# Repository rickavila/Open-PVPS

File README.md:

# Open-PVPS
Open Source Pandemic Virus Protection Systems

Our goal is to develop open source pandemic virus protection technology that will significantly improve the safety of healthcare workers on the front lines of COVID-19.

To achieve this we are working to substantially reduce the manufacturing and operating cost of a PAPR (https://en.wikipedia.org/wiki/Powered_air-purifying_respirator) while maintaining HEPA filter efficiency (99.97% for 3um particles) with a design that can be easily mass produced anywhere in the world using standard commercial manufacturing machinery and automation. All work performed on this project is open source and freely available with a permissive open source license (CC BY-SA 4.0).

This repository contains a directory for "technical reports", a directory for CAD designs, and a directory for the electronics components. 

The technical reports directory contains documents that describe the technical work, calculations, and decisions that have been made for each major PAPR technical area. The major technical areas are:
* Overall PAPR System Specifications and Performance
* Face Shield, Visor, and Drape (coming soon)
* Power and Control Box
* Blower, Gauge, and Diffuser
* Filter

The CAD directory contains CAD files used to deveop the first PVPS prototypes. The file format is Autodesk Fusion 360. In the future we will also post STL files for anyone that would like to print out the 3D printed components.

The electronics directory contains files that define the physical circuit boards for the battery box and the program for the control board microprocessor. All of the electronics were designed by Jim Hannas with inputs from the team.

This project has a website at http://open-pvps.org

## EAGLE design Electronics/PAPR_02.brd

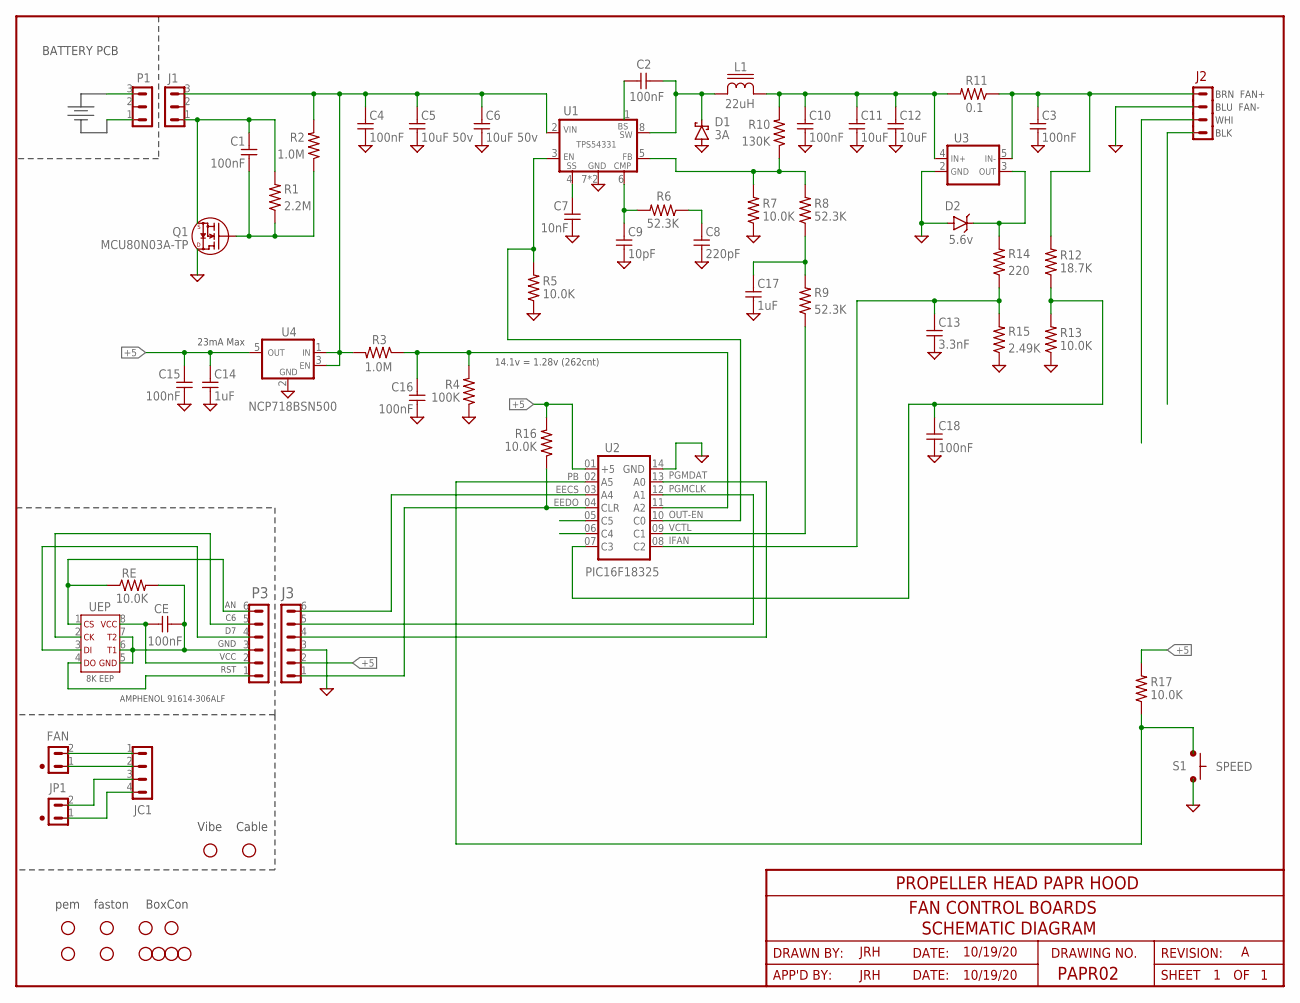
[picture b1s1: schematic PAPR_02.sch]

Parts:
BOM1, BOM2: pem; BOM_ADDER; PART_NUMBER KF2-440-ET
BOM3, BOM4: faston; BOM_ADDER; PART_NUMBER 4901
BOM5: vibrator; BOM_ADDER; PART_NUMBER Z6SCAB0061141
BOM6: BoxCon; BOM_ADDER; PART_NUMBER T4070014041-001
BOM7: Cable; BOM_ADDER; PART_NUMBER 1-2273003-1
BOM8: Plug; BOM_ADDER; PART_NUMBER 1445022-4
BOM9, BOM10, BOM11, BOM12: Pin; BOM_ADDER; PART_NUMBER 1-794606-1
C1, C2, C3, C4, C10, C15, C16, C18: 100nF; R0805; PART_NUMBER CL21B104KBC5PNL 08055C104KAT4A
C5, C6: 10uF 50v; R1210; PART_NUMBER C3225X7R1H106M250AC
C7: 10nF; R0805; PART_NUMBER CL21B103KBANNNC C0805C103K1RAC7210
C8: 220pF; R0805; PART_NUMBER CL21C221JBANNNC C0805C0G500-221JNE
C9: 10pF; R0805; PART_NUMBER C0805C100K5GACTU CML0805C0G100JT50V
C11, C12: 10uF; R1210; PART_NUMBER CL32A106KAULNNE TMK325BJ106KN-T
C13: 3.3nF; R0805; PART_NUMBER C0805C332K5RACTU
C14, C17: 1uF; R0805; PART_NUMBER CL21B105KOFNNNG EMK212B7105KG-T
CE: 100nF; R0805; PART_NUMBER CL21B104KBC5PNL 08055C104KAT4A
D1: 3A; SMA; PART_NUMBER B340A-13-F MBRA340T3G SSA34HE3_A/I
D2: 5.6v; SOT23-3; PART_NUMBER SZBZX84-C5V6LT1G
FAN: Fan_Hdr; 641215-2
J1: bat; 1746142
J2-BLK, J2-BLU, J2-BRN, J2-WHI: WIRE-HDRS200; PADS200
J3: 6p; J06P; PART_NUMBER MTSW-106-22-G-S-350
JC1: Cable_Termination; B4P-VH
JP1: Spare; 641215-2
L1: 22uH; SRU1048
P1: bat; 1746142M
P3: 6p plug; J06P
Q1: MCU80N03A-TP; TO252; PART_NUMBER MCU80N03A-TP DMG4800LK3-13 NTD4969NT4G
R1: 2.2M; R0805; PART_NUMBER RMCF0805FT2M21 CRCW08052M20FKEA
R2: 1.0M; R0805; PART_NUMBER RMCF0805FG1M00 RK73H2ATTD1004F
R3: 1.0M; R0805; PART_NUMBER RMCF0805FT2M21 CRCW08052M20FKEA
R4: 100K; R0805; PART_NUMBER RMCF0805FG100K RK73H2ATTD1003F
R5, R7, R13, R16, R17: 10.0K; R0805; PART_NUMBER RMCF0805FT10K0 RK73H2ATTD1002F
R6, R8, R9: 52.3K; R0805; PART_NUMBER RC0805FR-0752K3L CRCW080552K3FKEA
R10: 130K; R0805; PART_NUMBER RK73H2ATTD1303F RC0805FR-07130KL
R11: 0.1; R2512; PART_NUMBER CSRN2512FTR100
R12: 18.7K; R0805; PART_NUMBER RMCF0805FT18K7 RC0805FR0718K7L
R14: 220; R0805; PART_NUMBER RMCF0805FT220R RK73H2ATTD2200F
R15: 2.49K; R0805; PART_NUMBER RMCF0805FT2K49 CRCW08052K49FKEA
RE: 10.0K; R0805; PART_NUMBER RMCF0805FT10K0 RK73H2ATTD1002F
S1: SPEED; EVQ-P7C01P
U1: TPS54331; SO08PW
U2: PIC16F18325; SOIC14; PART_NUMBER PIC16F18325-I/SL
U3: ZXCT1010; SOT23-5
U4: NCP718BSN500; SOT23-5; PART_NUMBER NCP718BSN500T1G
UEP: 4K EEP; SO08; PART_NUMBER BR93H76RFJ-2CE

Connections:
+5: C14.1, C15.1, J3.2, R16.1, R17.1, U2.01 (VCC), U4.5 (OUT)
BAT+: C4.1, C5.1, C6.1, J1.3, R2.1, R3.1, U1.2 (VIN), U4.1 (IN), U4.3 (EN)
BAT-: C1.1, J1.1, Q1.2 (S), R1.1
BATT+: P1.3
BATT-: P1.1
BOOST: C2.1, U1.1 (BS)
CMP: C9.1, R6.1, U1.6 (CMP)
ECK: P3.5, UEP.2 (SK)
ECS: P3.6, RE.2, UEP.1 (CS)
EDI: P3.4, UEP.3 (DI)
EDO: P3.1, UEP.4 (DO)
EECS: J3.6, U2.03 (A4)
EEDO: J3.1, R16.2, U2.04 (CLR)
EGND: CE.2, P3.3, RE.1, UEP.5 (GND), UEP.6 (T1), UEP.7 (T2)
FB: R7.1, R8.1, R10.2, U1.5 (FB)
GND: C3.2, C4.2, C5.2, C6.2, C7.2, C8.2, C9.2, C10.2, C11.2, C12.2, C13.2, C14.2, C15.2, C16.2, C17.2, C18.2, D1.A, D2.1 (A), J2-BLU.1, J3.3, Q1.3 (D), R4.2, R5.2, R7.2, R13.2, R15.2, S1.1, S1.2 (1), U1.7 (GND), U1.9 (GND), U2.14 (GND), U3.2 (GND), U4.2 (GND)
IFAN: C13.1, R14.2, R15.1, U2.08 (C2)
J2-3: J2-WHI.1
J2-4: J2-BLK.1
unnamed: C1.2, Q1.1 (G), R1.2, R2.2
unnamed: CE.1, P3.2, UEP.8 (VCC)
unnamed: C3.1, J2-BRN.1, R11.2, R12.1, U3.5 (IN-)
unnamed: C18.1, R12.2, R13.1, U2.07 (C3)
unnamed: D2.3 (C), R14.1, U3.3 (OUT)
unnamed: C8.1, R6.2
unnamed: FAN.2, JC1.1
unnamed: FAN.1, JC1.2
unnamed: JC1.3, JP1.2
unnamed: JC1.4, JP1.1
OUT+: C10.1, C11.1, C12.1, L1.2, R10.1, R11.1, U3.4 (IN+)
OUT-EN: R5.1, U1.3 (EN), U2.10 (C0)
PB: R17.2, S1.3 (2), S1.4 (2), U2.02 (A5)
PGMCLK: J3.5, U2.12 (A1)
PGMDAT: J3.4, U2.13 (A0)
PWMF: C17.1, R8.2, R9.1
SS: C7.1, U1.4 (SS)
SW: C2.2, D1.C, L1.1, U1.8 (SW)
U2-05: U2.05 (C5)
U2-06: U2.06 (C4)
VBAT: C16.1, R3.2, R4.1, U2.11 (A2)
VCTL: R9.2, U2.09 (C1)

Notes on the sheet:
PROPELLER HEAD PAPR HOOD
FAN CONTROL BOARDS
SCHEMATIC DIAGRAM
PAPR02
JRH
10/19/20
pem
faston
BATTERY PCB
8K EEP
RST
VCC
GND
AMPHENOL 91614-306ALF
BRN FAN+
BLU FAN-
WHI
BLK
23mA Max
14.1v = 1.28v (262cnt)
Vibe
BoxCon
Cable

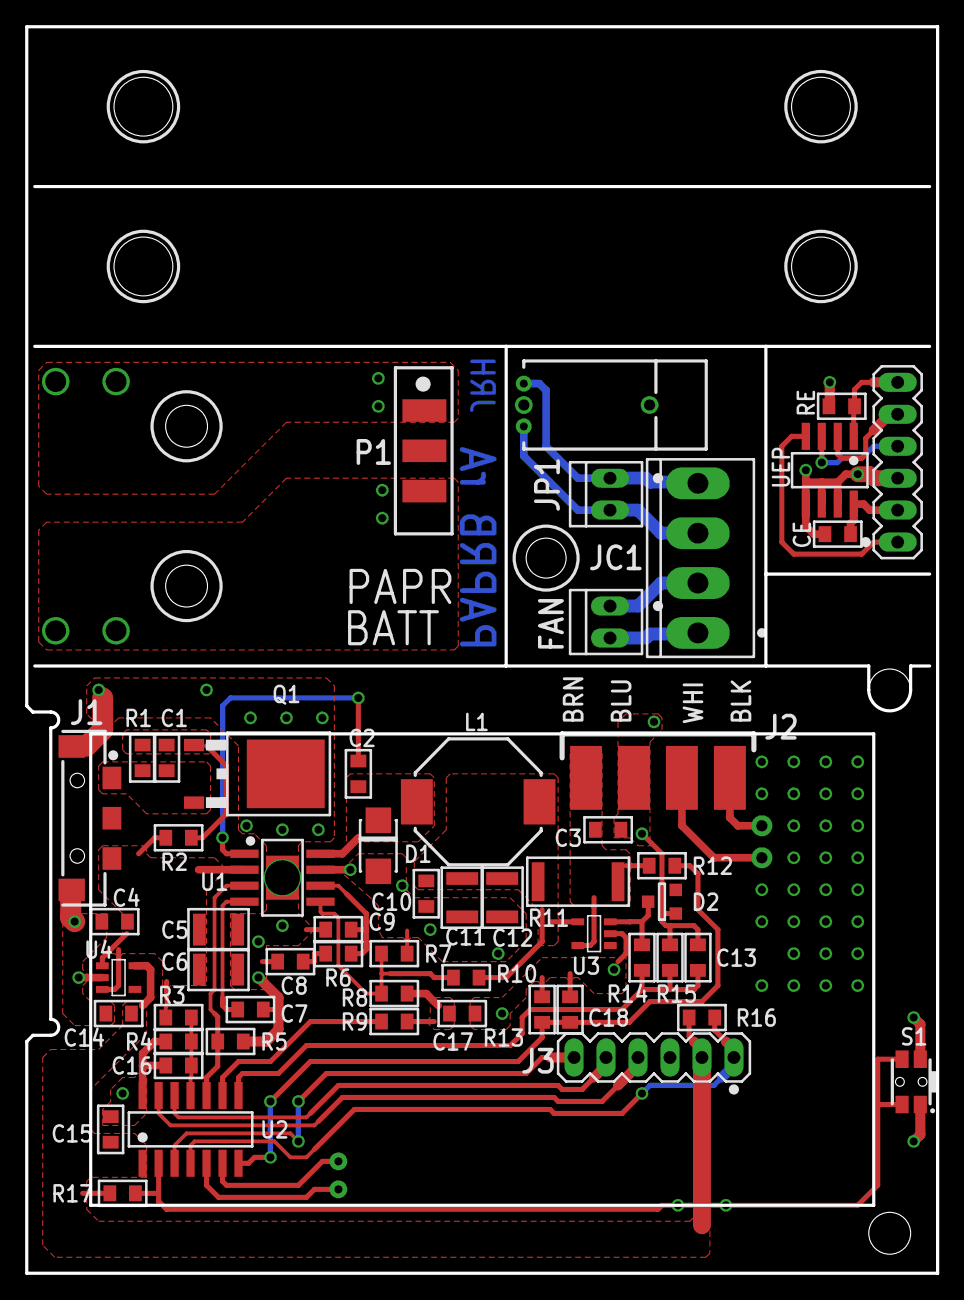
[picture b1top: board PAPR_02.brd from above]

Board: 2 copper layers, 72.4 x 99.1 mm, 70 parts (0 on the bottom side), 35 nets.

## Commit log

2020-05-29 First readme
2020-05-30 Create PVP v 1.3.1 Suspension .f3z
    This Fusion 360 file contains both the PVP1.3.1 face shield and the face shield adapter (holds 3M head gear to face shield).
2020-05-30 Moved faceshield adapter
    Moved faceshield adapter to the face shield directory.
2020-05-30 Changed the name of the head gear suspension
    because Bob wanted it that way...
2020-05-30 Added a readme
2020-05-30 Removed extra file extension
2020-10-11 Added the latest PVP CAD design containing all major components.
2020-10-11 Modified the Readme.md
2020-10-11 Fixed wording in the Readme.md
2021-03-15 First Technical Notes
    Adding technical notes for blower and filter.
2021-03-15 Update README.md
    Added more info on what is in the repository.
2021-03-15 Update README.md
    Added an image
2021-03-16 Reorganized documents into directories
2021-03-16 Added SystemSpecsAndPerf TechnicalReport
2021-03-16 Added a document that includes all current technical reports.
2021-03-16 Updated the Readme.md to add a description of the Electronics directory.
2021-03-16 Indicated that the face shield, visor and drape technical report is coming soon.
2021-03-16 Electronics files provided by Jim Hannas
2021-03-16 Added website address.
2021-03-16 minor change.
2021-03-17 Added the right license.
2021-03-29 PVP 1.3.6 All Parts with Slim Filter Adapter Design
